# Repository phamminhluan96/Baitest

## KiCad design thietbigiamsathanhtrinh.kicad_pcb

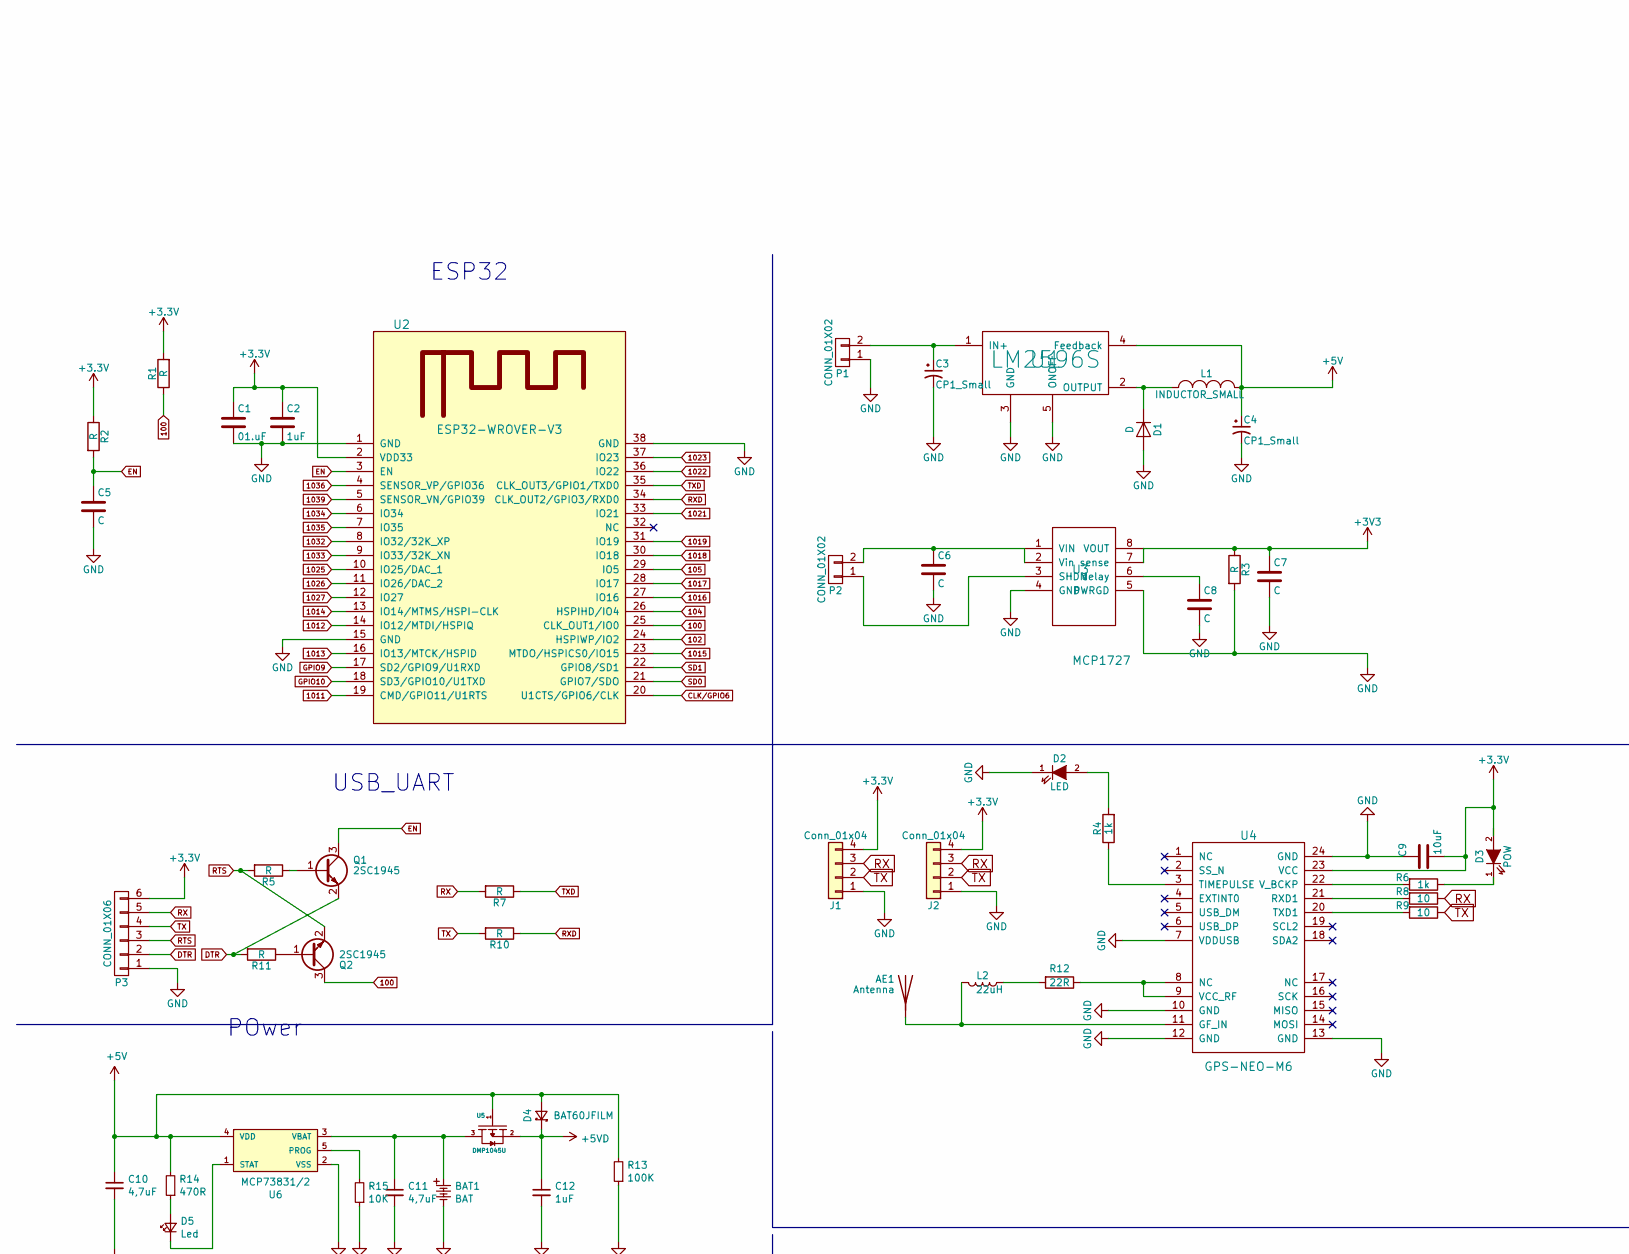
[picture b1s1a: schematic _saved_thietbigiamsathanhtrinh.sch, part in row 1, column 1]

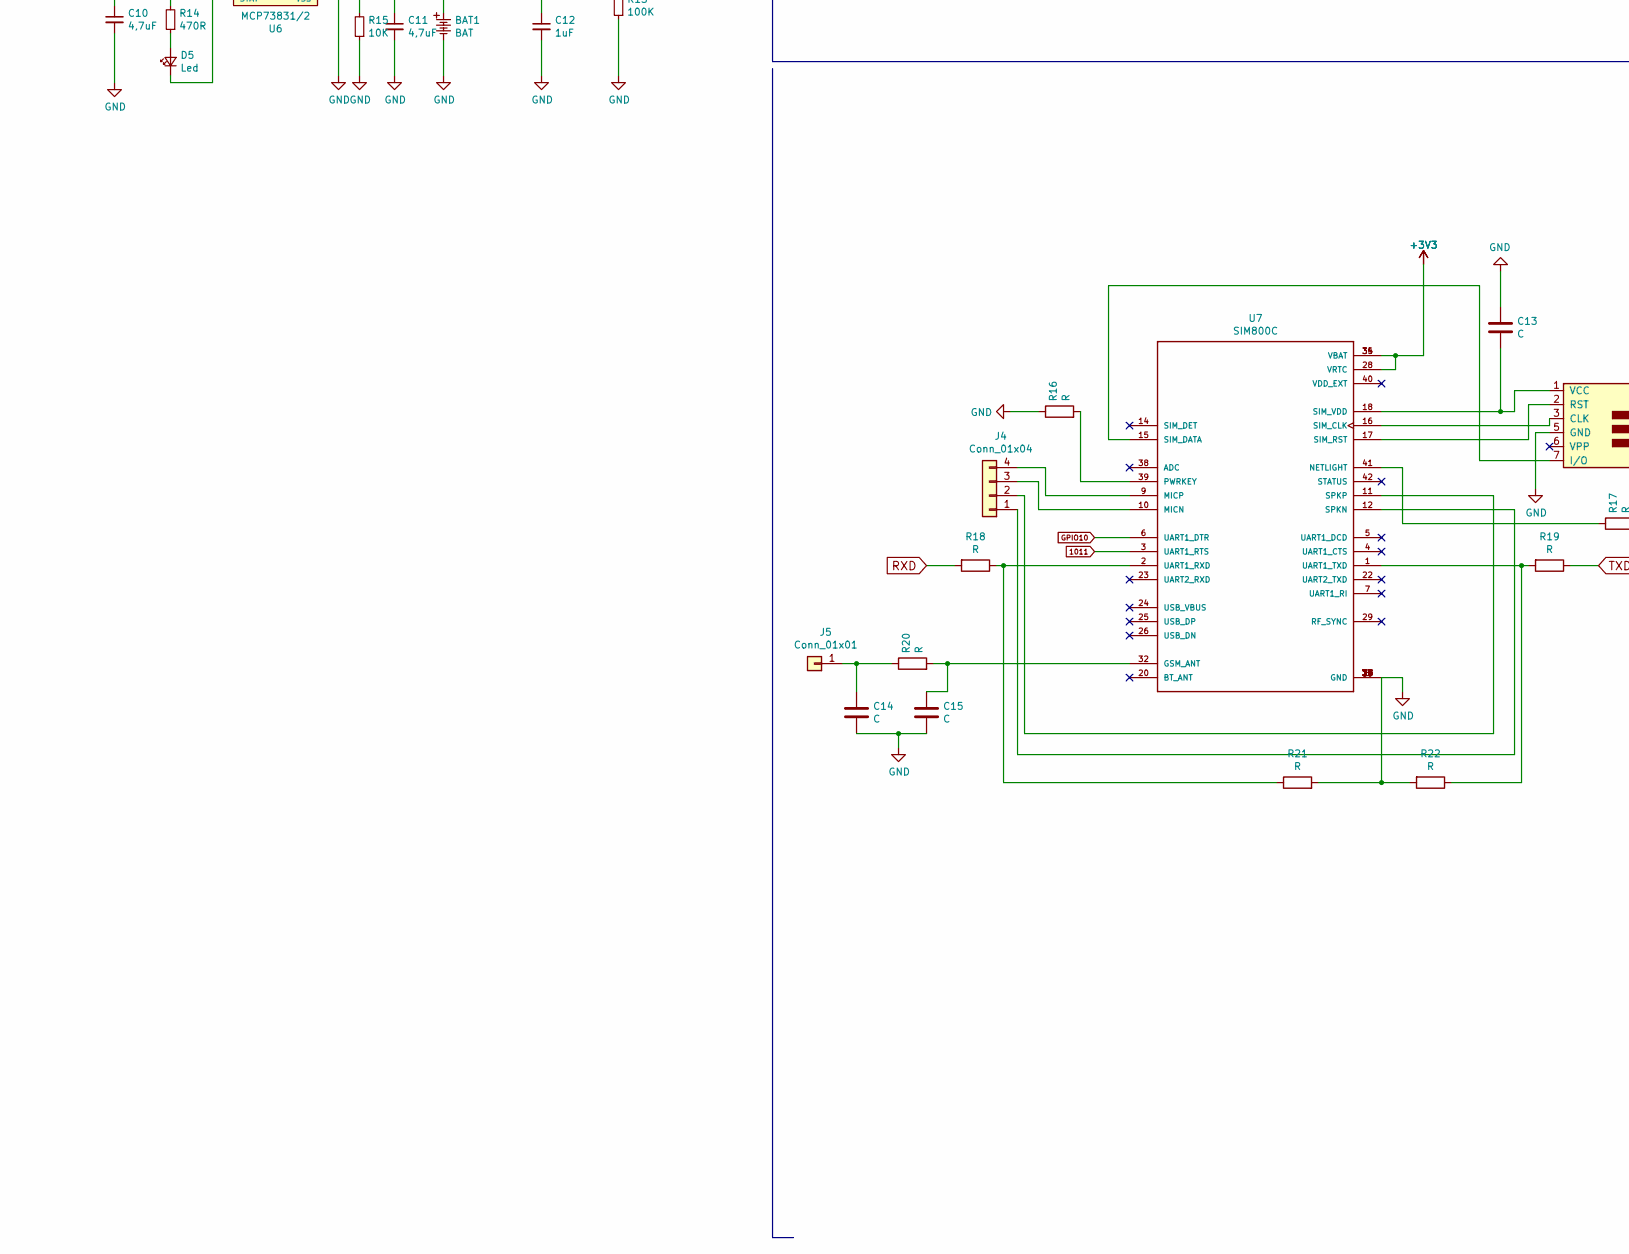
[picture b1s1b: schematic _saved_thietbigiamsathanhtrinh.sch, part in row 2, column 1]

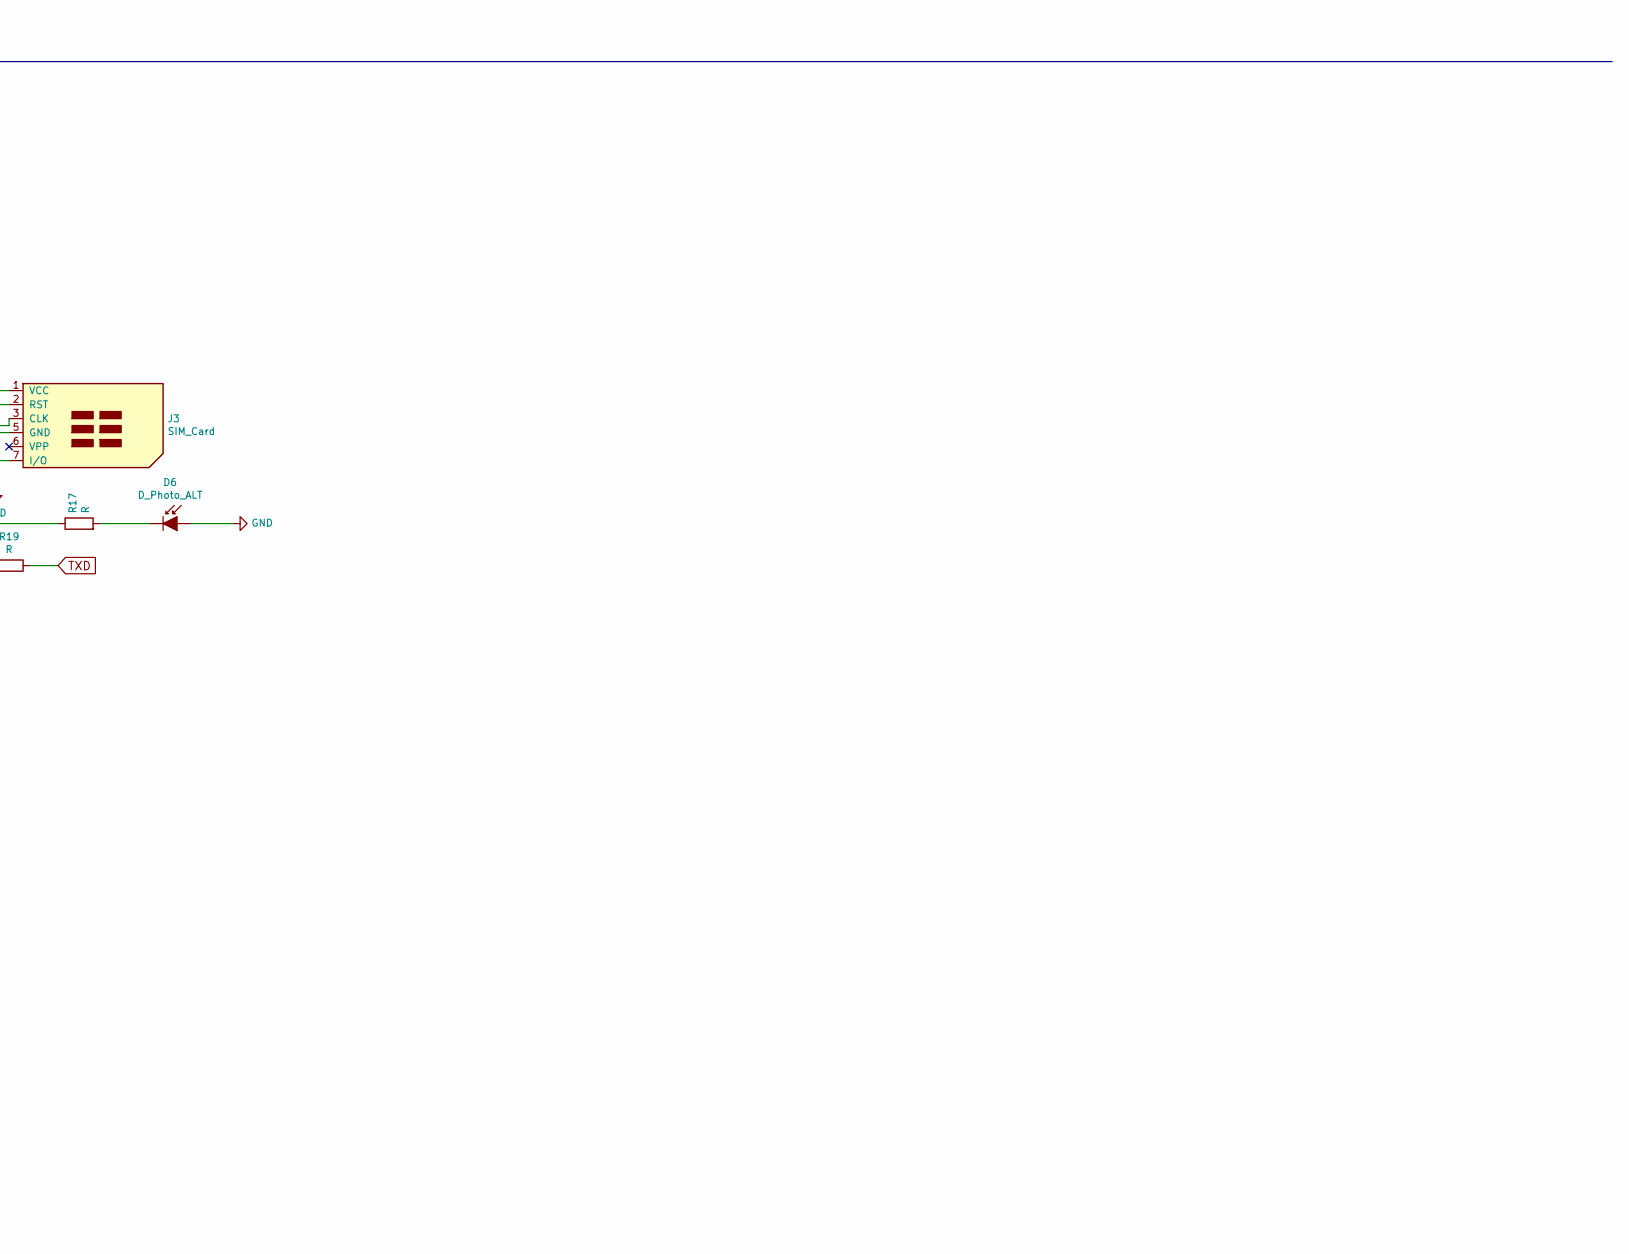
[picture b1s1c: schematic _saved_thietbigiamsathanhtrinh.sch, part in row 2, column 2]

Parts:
AE1: Antenna; 1pin
BAT1: BAT; Pin_Header_Straight_2x01_Pitch1.00mm_SMD
C1: 01.uF; C_0603
C2, C12: 1uF; C_0603
C3, C4: CP1_Small; C_0603
C5, C6, C7, C8, C13, C14, C15: C; C_0603
C9: 10uF; C_0603
C10, C11: 4,7uF; C_0603
D1: D; LED_0603
D2: LED; LED_0603_HandSoldering
D3: POW; LED_0603_HandSoldering
D4: BAT60JFILM; LED_0603
D5: Led; LED_0603
D6: D_Photo_ALT; LED_0603_HandSoldering
J1, J2, J4: Conn_01x04; PJ320D_3.5mm_Jack
J3: SIM_Card
J5: Conn_01x01; Pin_Header_Straight_1x01_Pitch2.00mm
L1: INDUCTOR_SMALL; L_0201
L2: 22uH; L_0201
P1, P2: CONN_01X02; Pin_Header_Straight_2x01_Pitch1.00mm_SMD
P3: CONN_01X06; Hirose_DF13C-06P-1.25V_06x1.25mm_Straight
Q1, Q2: 2SC1945; SOT-23
R1, R2, R3, R5, R7, R10, R11, R16, R17, R18, R19, R20, R21, R22: R; R_0603
R4, R6: 1k; R_0603
R8, R9: 10; R_0603
R12: 22R; R_0603
R13: 100K; R_0603
R14: 470R; R_0603
R15: 10K; R_0603
U1: LM2596S; TO-263-5_TabPin3
U2: ESP32-WROVER-V3; esp32-wrover-32S
U3: MCP1727; SC-70-8
U4: GPS-NEO-M6; SOIC-24
U5: DMP1045U; SOT-23
U6: MCP73831/2; SOT-23-5
U7: SIM800C

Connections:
100: Q2.3 (C), R1.1, U2.25 (CLK_OUT1/IO0)
102: U2.24 (HSPIWP/IO2)
104: U2.26 (HSPIHD/IO4)
105: U2.29 (IO5)
1011: U2.19 (CMD/GPIO11/U1RTS), U7.3 (UART1_RTS)
1012: U2.14 (IO12/MTDI/HSPIQ)
1013: U2.16 (IO13/MTCK/HSPID)
1014: U2.13 (IO14/MTMS/HSPI-CLK)
1015: U2.23 (MTDO/HSPICS0/IO15)
1016: U2.27 (IO16)
1017: U2.28 (IO17)
1018: U2.30 (IO18)
1019: U2.31 (IO19)
1021: U2.33 (IO21)
1022: U2.36 (IO22)
1023: U2.37 (IO23)
1025: U2.10 (IO25/DAC_1)
1026: U2.11 (IO26/DAC_2)
1027: U2.12 (IO27)
1032: U2.8 (IO32/32K_XP)
1033: U2.9 (IO33/32K_XN)
1034: U2.6 (IO34)
1035: U2.7 (IO35)
1036: U2.4 (SENSOR_VP/GPIO36)
1039: U2.5 (SENSOR_VN/GPIO39)
+5V: C4.1, C10.1, D4.2 (A), L1.2, R13.2, R14.2, U1.4 (Feedback), U5.1, U6.4 (VDD)
+5VD: C12.1, D4.1 (K), U5.2
CLK/GPIO6: U2.20 (U1CTS/GPIO6/CLK)
DTR: P3.2, Q1.2 (E), R11.2
EN: C5.1, Q1.3 (C), R2.2, U2.3 (EN)
GND: BAT1.2, C1.2, C2.2, C3.2, C4.2, C5.2, C6.2, C7.2, C8.2, C9.2, C10.2, C11.2, C12.2, C13.1, C14.2, C15.2, D1.2 (A), D2.1 (K), D6.2 (A), J1.1, J2.1, J3.5 (GND), P1.1, P3.1, R3.2, R13.1, R15.1, R16.1, R21.2, R22.2, U1.3 (GND), U1.5 (ONOFF), U2.1 (GND), U2.15 (GND), U2.38 (GND), U3.4 (GND), U3.5 (PWRGD), U4.7 (VDDUSB), U4.10 (GND), U4.12 (GND), U4.13 (GND), U4.24 (GND), U6.2 (VSS), U7.8 (GND), U7.13 (GND), U7.19 (GND), U7.21 (GND), U7.27 (GND), U7.30 (GND), U7.31 (GND), U7.33 (GND), U7.36 (GND), U7.37 (GND)
GPIO9: U2.17 (SD2/GPIO9/U1RXD)
GPIO10: U2.18 (SD3/GPIO10/U1TXD), U7.6 (UART1_DTR)
unnamed: AE1.1, L2.2, U4.11 (GF_IN)
unnamed: BAT1.1, C11.1, U5.3, U6.3 (VBAT)
unnamed: C3.1, P1.2, U1.1 (IN+)
unnamed: C6.1, P2.2, U3.1 (VIN), U3.2 (Vin)
unnamed: C8.1, U3.6 (delay)
unnamed: C13.2, J3.1 (VCC), U7.18 (SIM_VDD)
unnamed: C14.1, J5.1, R20.1
unnamed: C15.1, R20.2, U7.32 (GSM_ANT)
unnamed: D1.1 (K), L1.1, U1.2 (OUTPUT)
unnamed: D2.2 (A), R4.2
unnamed: D3.1 (K), R6.1
unnamed: D5.1 (K), U6.1 (STAT)
unnamed: D5.2 (A), R14.1
unnamed: D6.1 (K), R17.2
unnamed: J3.2 (RST), U7.17 (SIM_RST)
unnamed: J3.3 (CLK), U7.16 (SIM_CLK)
unnamed: J3.7 (I/O), U7.15 (SIM_DATA)
unnamed: J4.1, U7.12 (SPKN)
unnamed: J4.2, U7.11 (SPKP)
unnamed: J4.3, U7.10 (MICN)
unnamed: J4.4, U7.9 (MICP)
unnamed: L2.1, R12.2
unnamed: P2.1, U3.3 (SHDN)
unnamed: Q1.1 (B), R5.1
unnamed: Q2.1 (B), R11.1
unnamed: R4.1, U4.3 (TIMEPULSE)
unnamed: R6.2, U4.22 (V_BCKP)
unnamed: R8.2, U4.21 (RXD1)
unnamed: R9.2, U4.20 (TXD1)
unnamed: R12.1, U4.8 (NC), U4.9 (VCC_RF)
unnamed: R15.2, U6.5 (PROG)
unnamed: R16.2, U7.39 (PWRKEY)
unnamed: R17.1, U7.41 (NETLIGHT)
unnamed: R18.1, R21.1, U7.2 (UART1_RXD)
unnamed: R19.2, R22.1, U7.1 (UART1_TXD)
RTS: P3.3, Q2.2 (E), R5.2
RX: J1.3, J2.3, P3.5, R7.2, R8.1
RXD: R10.1, R18.2, U2.34 (CLK_OUT2/GPIO3/RXD0)
SD0: U2.21 (GPIO7/SDO)
SD1: U2.22 (GPIO8/SD1)
TX: J1.2, J2.2, P3.4, R9.1, R10.2
TXD: R7.1, R19.1, U2.35 (CLK_OUT3/GPIO1/TXD0)

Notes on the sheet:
ESP32
USB_UART
POwer

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
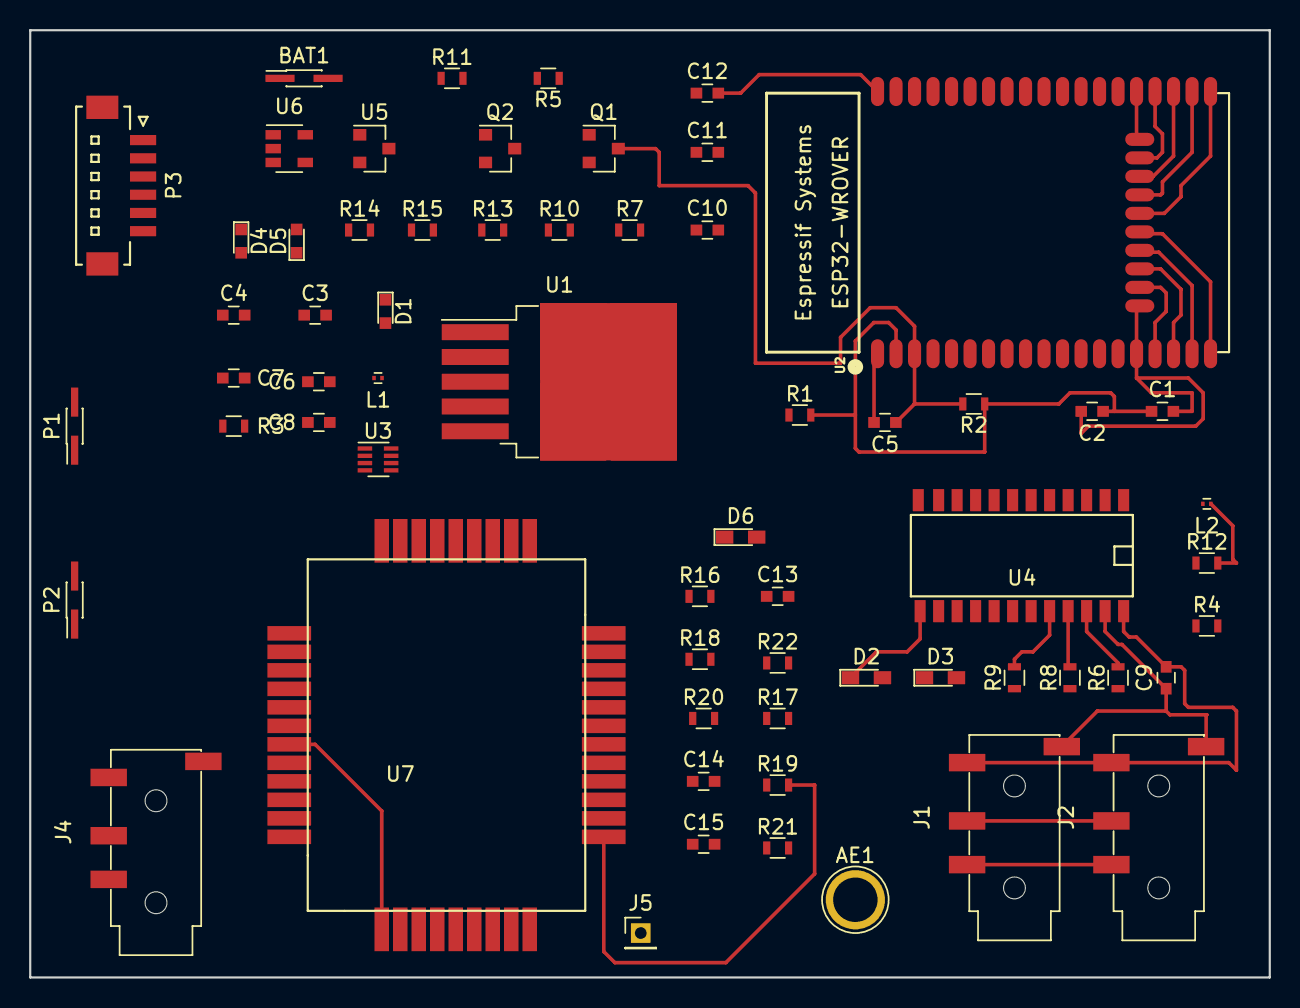
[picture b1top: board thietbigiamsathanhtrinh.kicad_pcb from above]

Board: 2 copper layers, 85.1 x 65.0 mm, 63 parts (0 on the bottom side), 46 nets.
